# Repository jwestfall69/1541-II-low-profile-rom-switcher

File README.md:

# 1541-II-low-profile-rom-switcher
* [Overview](#overview)
* [Hardware](#hardware)
   * [PCB Manufacturing](#pcb-manufacturing)
   * [BOM](#bom)
   * [Assembly](#assembly)
* [Programming The Board](#programming-the-board)
   * [Hardware](#hardware-1)
   * [Software](#software)
* [Programming The 27c512](#programming-the-27c512)
* [Installation](#installation)
   * [Reset Line (C64)](#reset-line-c64)
   * [Testing Cut Pins](#testing-cut-pins)
   * [Reset Line (1541-II)](#reset-line-1541-ii)
* [Debugging](#debugging)

## Overview
The 1541-II low profile rom switcher is designed to work in conjunction with [bwack](https://github.com/bwack)'s [SKS64](https://github.com/bwack/C64-Switchless-Multi-Kernal-27C256-adapter/) switchless kernel rom switcher for the C64.  SKS64 does have support for running in a 1541-II disk drive. However I found for my 1541-II it's not possible to use because its way to tall and gets in the way of the drive motor.

Thus I decided to make the low profile 1541-II board.  Here you can see the difference in height between them.

Board pics / Assembled

In order for the low profile board to work we need to take control of A14 (PIN 27) and A15 (PIN 1) on the 27c512 ROM.  These are normally tied to VCC on the 1541-II board.  To do this we cut these legs from the socket used on the low profile board to prevent them connecting to the 1541-II board.  This allows the ATtiny402 MCU to control those address lines on the 27c512 eprom for switching between kernels.

There are a few difference between the low profile board and SKS64 shortboard for use in a 1541-II.

  * Support for 4 kernels (SKS64 is hardcoded for 2)
  * NO LED support
  * Debug serial port
  * ATtiny 4x2 MCU (SKS64 uses ATtiny45/85)
  * Removal of Restore / EXROM pins (not needed in 1541-II)

## Hardware
#### PCB Manufacturing
You will want to pick **1.0mm PCB thickness** instead of the default of 1.6mm.  A 1.6mm thick PCB will make the legs a little to short and cause it to not be fully secure in the rom socket.

I've been using [jlcpcb](https://jlcpcb.com/) for PCB manufacturing.  Watch out as by default they will add an order number to the silk screen unless you tell them not to.

#### BOM
| Description | Part Number | DigiKey | Mouser | Notes |
|-------------|-------------|---------|--------|-------|
| ATtiny402 20Mhz | ATTINY402-SSN | [ATTINY402-SSN-NDD](https://www.digikey.com/en/products/detail/microchip-technology/ATTINY402-SSN/9947535) | [579-ATTINY402-SSN ](https://www.mouser.com/ProductDetail/Microchip-Technology/ATTINY402-SSN?qs=3HJ2avRr9PLRpVpK36KNsg%3D%3D) | Other ATtiny tinyAVR 0/1/2-series models should be viable as well.  The code compiles to a little under 2K in size.  So, it should be viable to use a ATtiny 2x2 model, but I've only tested with a 402 |
| 100nf / 0.1uf 50V SMD Ceramic Capacitor 0805 Size | CL21B104KBCNNNC | [1276-1003-2-ND](https://www.digikey.com/en/products/detail/samsung-electro-mechanics/CL21B104KBCNNNC/3886661)| [187-CL21B104KBCNNNC](https://www.mouser.com/ProductDetail/Samsung-Electro-Mechanics/CL21B104KBCNNNC?qs=349EhDEZ59pEfpnm5yBEmQ%3D%3D) | Other models should be fine with the same size/specs |
| 28 Pin Dip Machine Socket | ICM-628-1-GT-HT | [2057-ICM-628-1-GT-HT-ND](https://www.digikey.com/en/products/detail/adam-tech/ICM-628-1-GT-HT/9832982) | ?? | The specific part number isn't required, but it must be a machined 28 pin dip socket with the cross members in the same locations as seen in the picture at the top of this page. This [part](https://www.aliexpress.us/item/2251832711755702.html) (28pin wide) from Aliexpress also works |
| 27c512 eprom | | | | Not sure if there is a speed requirement, I've been using 120ns |
| 1x right angle IDC jumper pin | | | | |

#### Assembly
The first thing you should do is a test fit of the socket into the low profile PCB.  I came across a couple PCBs in a batch that didn't fit and wasn't until after I had soldered the SMD components that I found this out.

As you can see in the first socket in the picture below the pins start out wide then go skinny.  Normally the wide part is used to keep the socket up off a board, however the low profile PCB has extra wide through holes to allow it to sit flush with the plastic part of the socket.  Doing this allows the pins from the socket to be long enough to fit properly into the rom socket on the 1541-II board.

You should solder the SMD components first.  Take special care to void getting any solder into any of the socket through holes.

When soldering the socket its best to not use a ton of solder.  The below picture is a board where the socket hasn't been soldered in yet.

Note the small gap between the through holes and socket pins.  Solder will naturally want to wick up into that gap.  I generally just use enough solder so that the gap around the socket pin becomes filled.

Once you have completed soldering the socket you should check the skinny part of the pins to verify there aren't any solder blobs on them.  These could cause damage to the rom socket.

You will then want to cut the skinning part of the legs on the pins the arrows are pointing at on the underside of the low profile board as seen below.

Install the single right angle IDC jumper pin into the RESET/RX through hole so its pointing towards the commodore logo as seen in the picture at the top of this page.

## Programming The Board
#### Hardware
Programming is done with a UPDI programmer.  I've been using this one:

[Serial UPDI Programmer for ATmega 0-Series, or ATtiny 0-Series or 1-Series, or AVR DA or AVR DB](https://www.amazon.com/dp/B09X64YRLD?psc=1&ref=ppx_yo2ov_dt_b_product_details)

Note: This programmer (and likely others) has a switch for 3.3V and 5V.  Set it to 5V.

The rom switcher programming port is setup so you can wedge the pins from the above programmer directly into them to programming.

Of course be sure you properly orient the board so the labeled pin/holes match up.  vcc to vcc, gnd to gnd, and updi to updi.

#### Software
For software I've been using the [Arduino IDE](https://www.arduino.cc/en/software/OldSoftwareReleases) with [megaTinyCore](https://github.com/SpenceKonde/megaTinyCore), which adds support for tinyAVR 0/1/2-Series MCUs.

**NOTE**: The makers of megaTinyCore currently recommend using Arduino IDE version 1.8.13 for best compatibility.  2.0 definitely does not work!

To install the megaTinyCore you, should just need to add http://drazzy.com/package_drazzy.com_index.json to "Additional Boards Manager URLs" in the settings for the Arduino IDE.

From there you need to configure the board/programming settings.  I've been using these:

## Programming The 27c512
The low profile board expects a 27c512 eprom, which 64KB in size.  The kernel size of the 1541-II is 16KB, thus 4 banks (0 to 3) are support.

When the SKS64 switches to a new bank on the C64 it will send the selected bank number to the 1541-II board (using serial over the RESET line).  The low profile firmware will use this bank number to select the corresponding bank in the 27c512 eprom.

Things to consider with the SKS64 in the C64:

  * Longboard version with a 27c256 supports 4 banks (0 to 3)
  * Longboard version with a 27c512 supports 8 banks (0 to 7)
  * Shortboard version with a 27c256 supports 3 banks (1 to 3)
  * Shortboard version with a 27c512 supports 7 banks (1 to 7)

In the case where the low profile board is told to change to bank 4+ it will default to just picking the 3rd bank.  If you want a different behaviour you can tweak the firmware.

You will note that the shortboard versions of the SKS64 starts at bank 1 instead of 0.  In this case the low profile board will never use whatever kernel is placed into bank 0 of the 27c512, since SKS64 will never send 0.  You should take this in to account when setting up your 27c512 eprom.

```
dos> copy /b bank0_kernel.bin + bank1_kernel.bin + bank2_kernel.bin + bank3_kernel.bin low_profile_27c512.bin

linux $ cat bank0_kernel.bin bank1_kernel.bin bank2_kernel.bin bank3_kernel.bin > low_profile_27c512.bin
```

Then program your low_profile_27c512.bin to your 27c512 eprom.

## Installation
#### Reset Line (C64)
Some C64 models have a segmented RESET signals for internal (INTRES) and external (EXTRES).  The latter goes to the disk drive and only seems to trigger during a power up of the C64.  This prevents the SKS64 in the C64 from sending its rom switch command to the disk drive.

To work around this is possible to connect the INTRES and EXTRES lines together, so when the SKS64 in the C64 sends its rom switch command to the INTRES line it will also goto the EXTRES.

| C64 MODEL       | HAS SEGMENTED RESET   | WORK AROUND |
|:---------------:|:---------------------:|-------------|
| 326298 (long)   |         NO            | Not Needed  |
| 250407 (long)   |         NO            | Not Needed  |
| 250425 (long)   |        YES            | ?? / don't own this model |
| 250466 (long)   |        YES            | ?? / don't own this model |
| 250469 (short)  |        YES            | Bridge PIN 2 and 6 on U22 (7406N) |

#### Testing Cut Pins
Once you have the low profile board installed in the kernel rom socket you will want to verify the cut pins are not making contact with the underlying socket on the 1541-II board.

Use a multimeter on continuity mode and verify there is no continuity between PIN 28 (VCC) and the cut pins (PIN 1 and PIN 27).

#### Reset Line (1541-II)
SKS64 in the C64 communicates to the low profile board over the RESET line to tell it which 1541-II kernel rom to switch it.

There are a few places you can tap the RESET line, but the one below seems to be easiest.

Additionally I'm using the green disc capacitor to help hold the wire down.

## Debugging
The communication between the SKS64 in the C64 and the low profile board is one way, leaving the TX line of the ATtiny's UART available for debug output.

All you should need is a dumb usb to serial device like the one below.

The usb to serial device needs to have its RX connected to the low profile board's TX through hole and its GND to GND.

This connection does not need to be soldered, just have it at an angle so the pins are touching the side of the through holes.

From there you need to use a serial program connected at 19200 baud.  The arduino IDE has one built it, and is what I use.

I kept the debug output short as I was trying to keep the total firmware size under 2k, so its possible to use an ATtiny 2x2 instead of the 4x2.

These are what the debug values mean.

```
Ln  = At power up read 'n' from ATtiny's EEPROM indicating the last used rom bank
Sn  = Switched to rom bank 'n'
Wn  = Wrote 'n' to ATtiny's EEPROM
M   = Received magic byte (0xde) from SKS64
Rn  = Received request to switch to rom bank 'n' from SKS64
```

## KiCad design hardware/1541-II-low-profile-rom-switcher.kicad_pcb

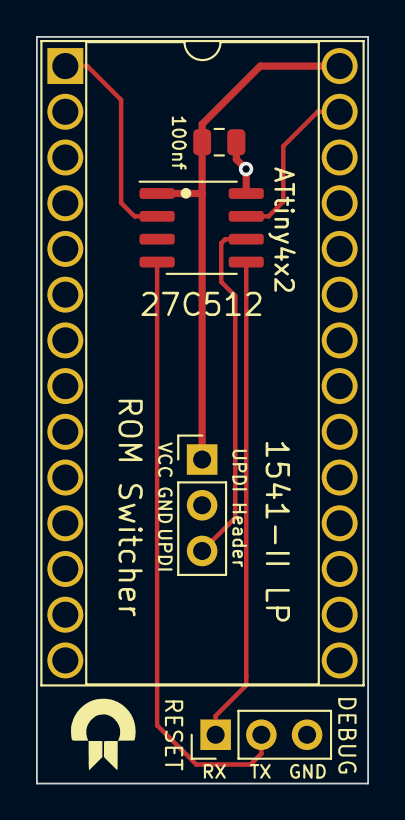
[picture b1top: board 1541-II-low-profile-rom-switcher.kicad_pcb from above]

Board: 2 copper layers, 18.4 x 41.5 mm, 5 parts (0 on the bottom side), 7 nets.

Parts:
C1: 100nf; C_0805_2012Metric
J1: UPDI Header; PinHeader_1x03_P2.54mm_Vertical
J2: UART; PinHeader_1x03_P2.54mm_Vertical
U1: 27C512; DIP-28_W15.24mm_Socket_Wide_Holes
U2: ATtiny402-SS; SOIC-8_3.9x4.9mm_P1.27mm

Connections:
/A14: U1.27 (A14), U2.7 (PA3)
/A15: U1.1 (A15), U2.2 (PA6)
/RX: J2.1, U2.5 (PA2)
/TX: J2.2, U2.4 (PA1)
/UPDI: J1.3, U2.6 (~RESET/PA0)
GND: C1.1, J1.2, J2.3, U1.14 (GND), U2.8 (GND)
VCC: C1.2, J1.1, U1.28 (VCC), U2.1 (VCC)

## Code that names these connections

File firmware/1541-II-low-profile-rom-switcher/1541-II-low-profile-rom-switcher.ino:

#include <EEPROM.h>

#define SKS64_MAGIC     0xde
#define MAX_BANK        3

#define A14             PIN_PA3
#define A15             PIN_PA6

void setup() {
  // Communication from sks64 in the c64 is one way to us over the drive's RESET
  // line. This leaves the UART's TX line available for us to use for serial
  // debug output from the ATtiny

  // This switches the UART to use it's alternate pins on the ATtiny, which are
  // more convenient for trace routing
  // RX = PA2 (pin 5) connected to the RESET port
  // TX = PA1 (pin 4) connected to the DEBUG port
  Serial.swap();
  Serial.begin(19200, SERIAL_8N1);

  pinMode(A14, OUTPUT);
  pinMode(A15, OUTPUT);
  
  setBank(loadBank());
}

uint8_t loadBank(void) {
  uint8_t bank = EEPROM.read(0);

  Serial.write('L');
  if(bank > MAX_BANK) {
    Serial.write('E');
    bank = 0;
  }
  Serial.write('0' + bank);
  
  return bank;
}

void setBank(uint8_t bank) {
  digitalWrite(A14, bank & 0x01);
  digitalWrite(A15, bank & 0x02);

  Serial.write('S');
  Serial.write('0' + bank);
}


void saveBank(uint8_t bank) {
  EEPROM.write(0, bank);
  Serial.write('W');
  Serial.write('0' + bank);
  Serial.println();
}

void loop() {
  
  if(!Serial.available()) {
    return;
  }

  // When sks64 in the c64 changes the rom bank in the c64 it will send 2 bytes to
  // the disk drive over the RESET line
  // 0xde = magic byte
  // 0x0n = bank it switched to (0 to 3 or 7 depending on the sks64's configuration)
  uint8_t magic = Serial.read();
  if(magic != SKS64_MAGIC) {
    return;
  }
  Serial.write('M');

  delay(1);
  
  if(!Serial.available()) {
    return;
  }

  uint8_t bank = Serial.read();
  Serial.write('R');
  Serial.print(bank, HEX);

  // Should we take some other action if the user is using a 8 kernel configuration
  // with the sks64 in the c64? Below will force kernels 5-8 to always get our 4th
  // kernel+dos bank
  if(bank > MAX_BANK) {
    bank = MAX_BANK;
  }
  
  setBank(bank);
  saveBank(bank);
}

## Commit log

2023-12-14 initial checkin
2023-12-27 Add docs
2024-01-01 Add docs about segmented RESET line on some C64 models
